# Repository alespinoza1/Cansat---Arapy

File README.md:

# Cansat - Arapy
Este repositorio contiene los archivos de diseño de placas electrónicas, modelos 3D, firmware y código fuente de la aplicación.

[proyecto arapy](http://www.proyectoarapy.com.py/)

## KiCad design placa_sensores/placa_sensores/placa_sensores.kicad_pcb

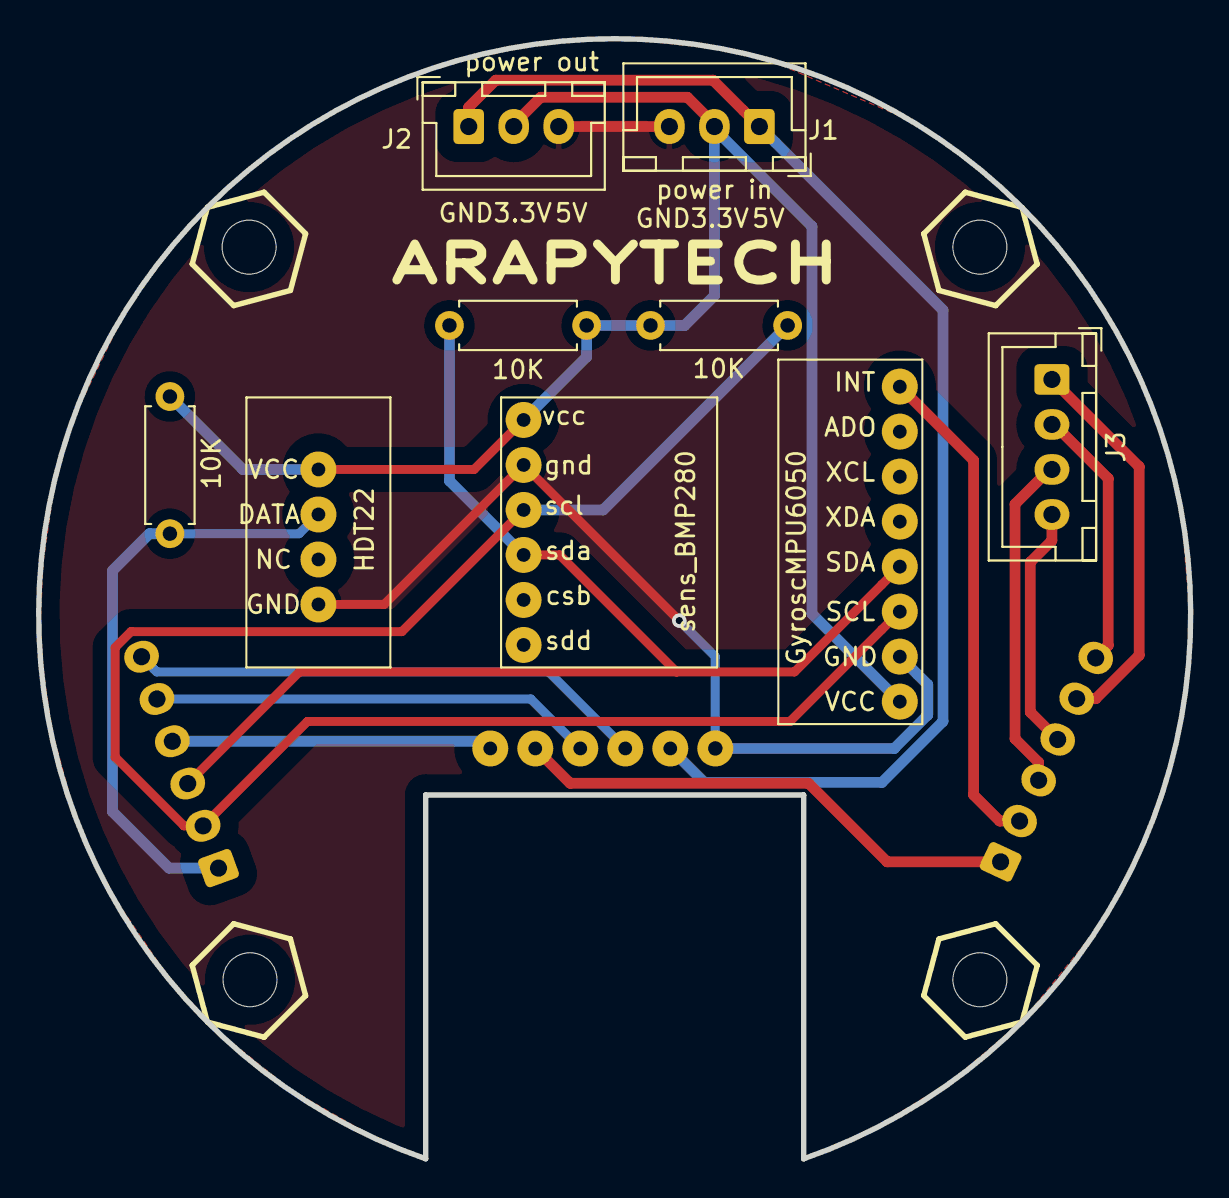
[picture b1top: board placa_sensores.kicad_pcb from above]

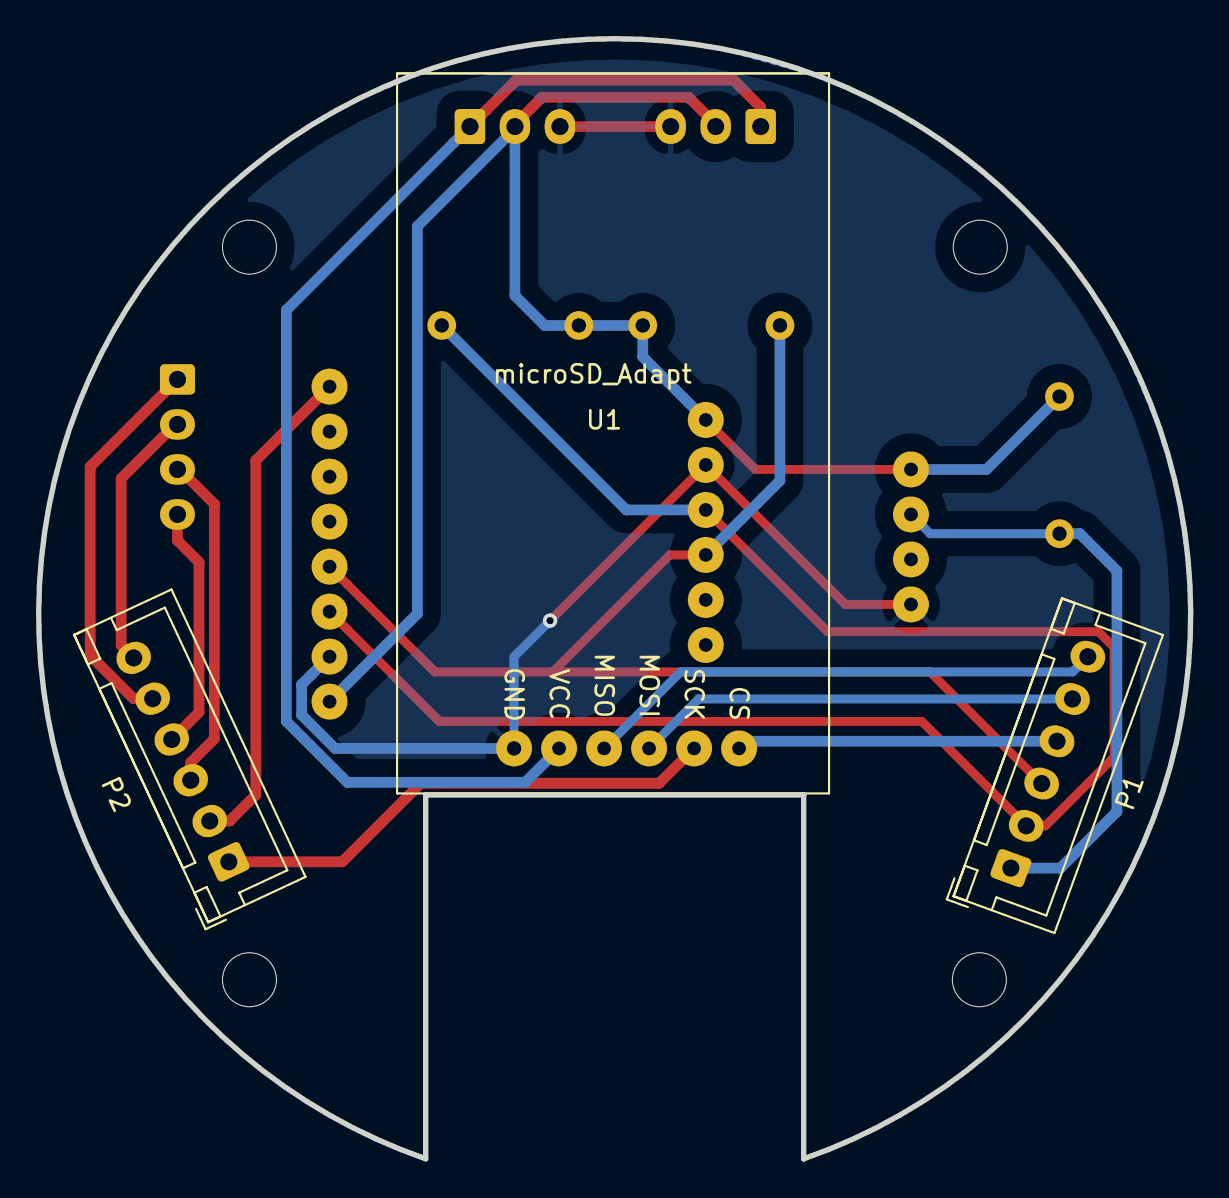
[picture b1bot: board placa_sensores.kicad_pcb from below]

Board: 2 copper layers, 64.0 x 62.2 mm, 10 parts (3 on the bottom side), 14 nets.

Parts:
10K, 10K#2: 10K; R_Axial_DIN0207_L6.3mm_D2.5mm_P7.62mm_Horizontal
10K#3: R; R_Axial_DIN0207_L6.3mm_D2.5mm_P7.62mm_Horizontal
HDT22: Sens_DHT22; DHT22
J1: power in; JST_XH_B3B-XH-A_1x03_P2.50mm_Vertical
J2: power out; JST_XH_B3B-XH-A_1x03_P2.50mm_Vertical
J3: Conn_01x04; JST_XH_B4B-XH-A_1x04_P2.50mm_Vertical
P1: Conector Señales 1; JST_XH_B6B-XH-A_1x06_P2.50mm_Vertical
P2: Conector Señales 2; JST_XH_B6B-XH-A_1x06_P2.50mm_Vertical
U1: microSD_Adapt; microSD

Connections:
3.3V: 10K.1, 10K#2.1, 10K#3.1, HDT22.1, J1.2, J2.2
5V: J1.1, J2.1, U1.2
CS: P1.4, U1.6
DGND: HDT22.4, J1.3, J2.3, U1.1
Dig1: J3.3, P2.3
MISO: P1.6, U1.3
MOSI: P1.5, U1.4
PWM: J3.4, P2.4
RESC: J3.2, P2.6
SCK: P2.1, U1.5
SCL: 10K.2, P1.2
SDA: 10K#2.2, P1.3
TEMP_SENS: 10K#3.2, HDT22.2, P1.1
TRANS: J3.1, P2.5

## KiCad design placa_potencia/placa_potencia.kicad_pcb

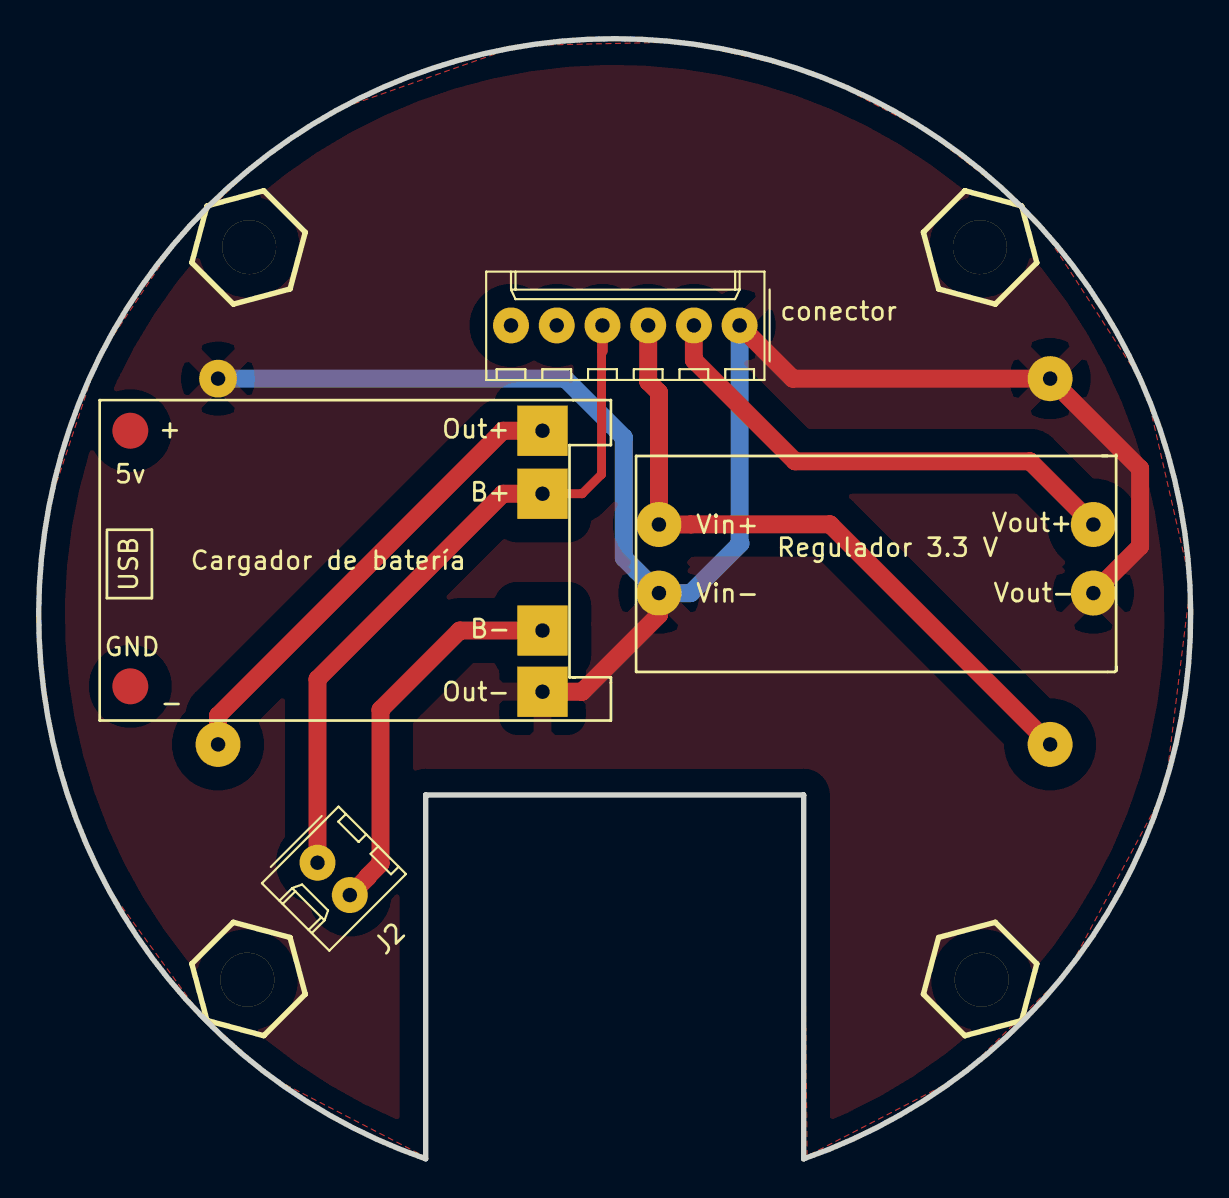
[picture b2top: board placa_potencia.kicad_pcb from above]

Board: 2 copper layers, 64.0 x 62.2 mm, 4 parts (1 on the bottom side), 4 nets.

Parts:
Elevador Boost : boost_5V; dc_dc_conv_xl60009
J2: Conn_01x02; Molex_KK-254_AE-6410-02A_1x02_P2.54mm_Vertical
Regulador 3.3 V : reg3_3V; AMS117_3_3V_MOD
conector: Conn_01x06_Male; Molex_KK-254_AE-6410-06A_1x06_P2.54mm_Vertical

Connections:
+BATT: J2.1, conector.4
/3.3V: Regulador 3.3 V.3, conector.2
/7V: Elevador Boost.3, Regulador 3.3 V.1, conector.3
Earth: Elevador Boost.2, Elevador Boost.4, Regulador 3.3 V.2, Regulador 3.3 V.4, conector.1

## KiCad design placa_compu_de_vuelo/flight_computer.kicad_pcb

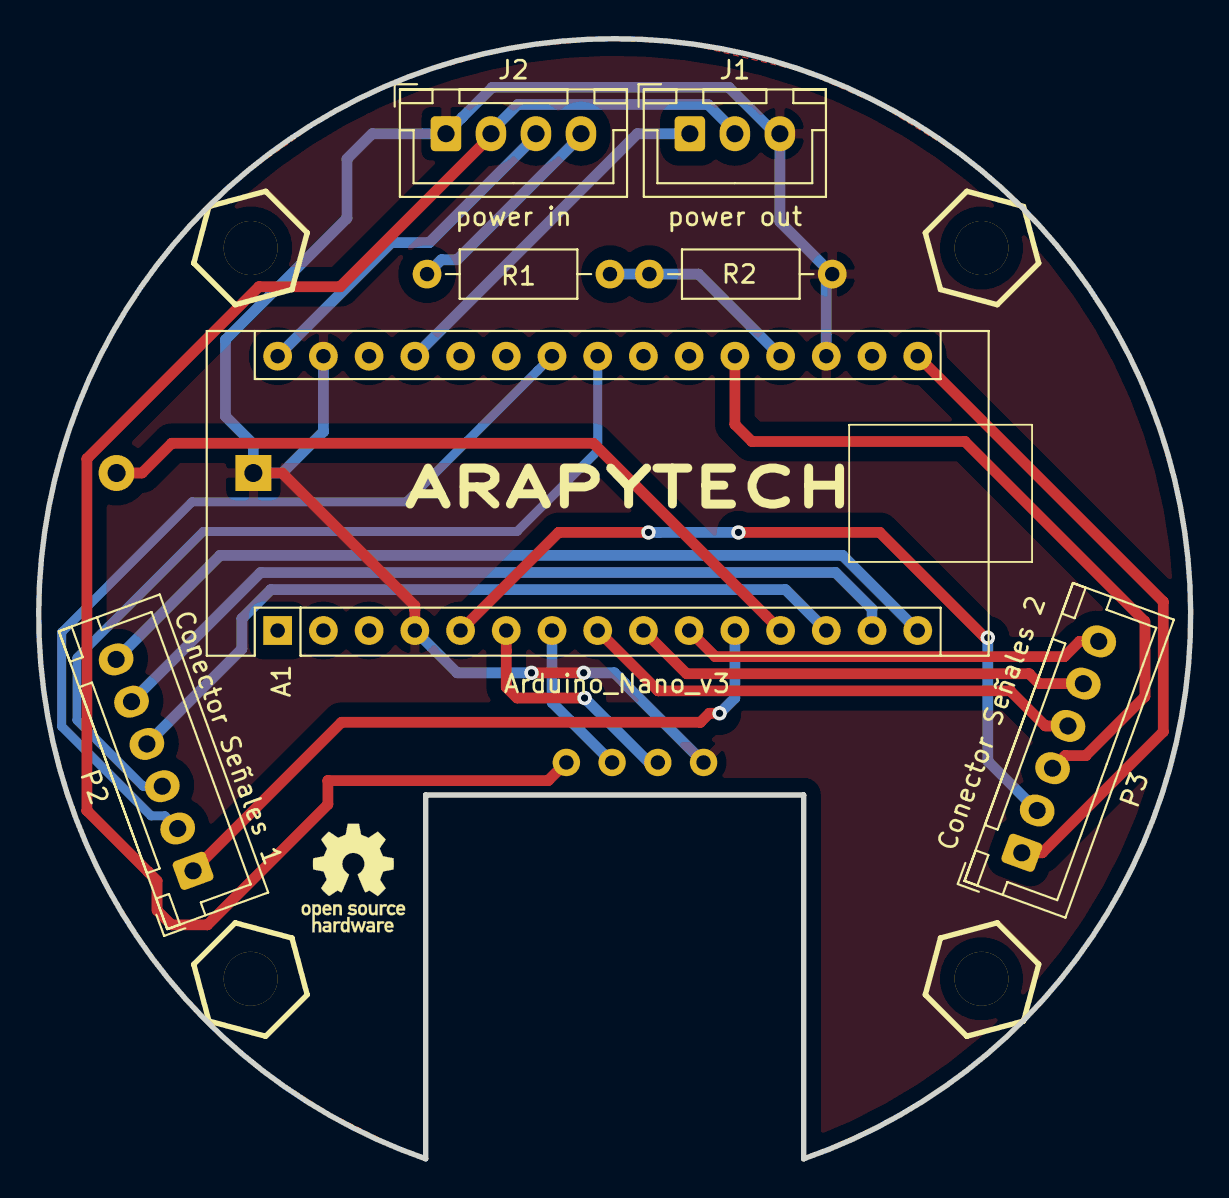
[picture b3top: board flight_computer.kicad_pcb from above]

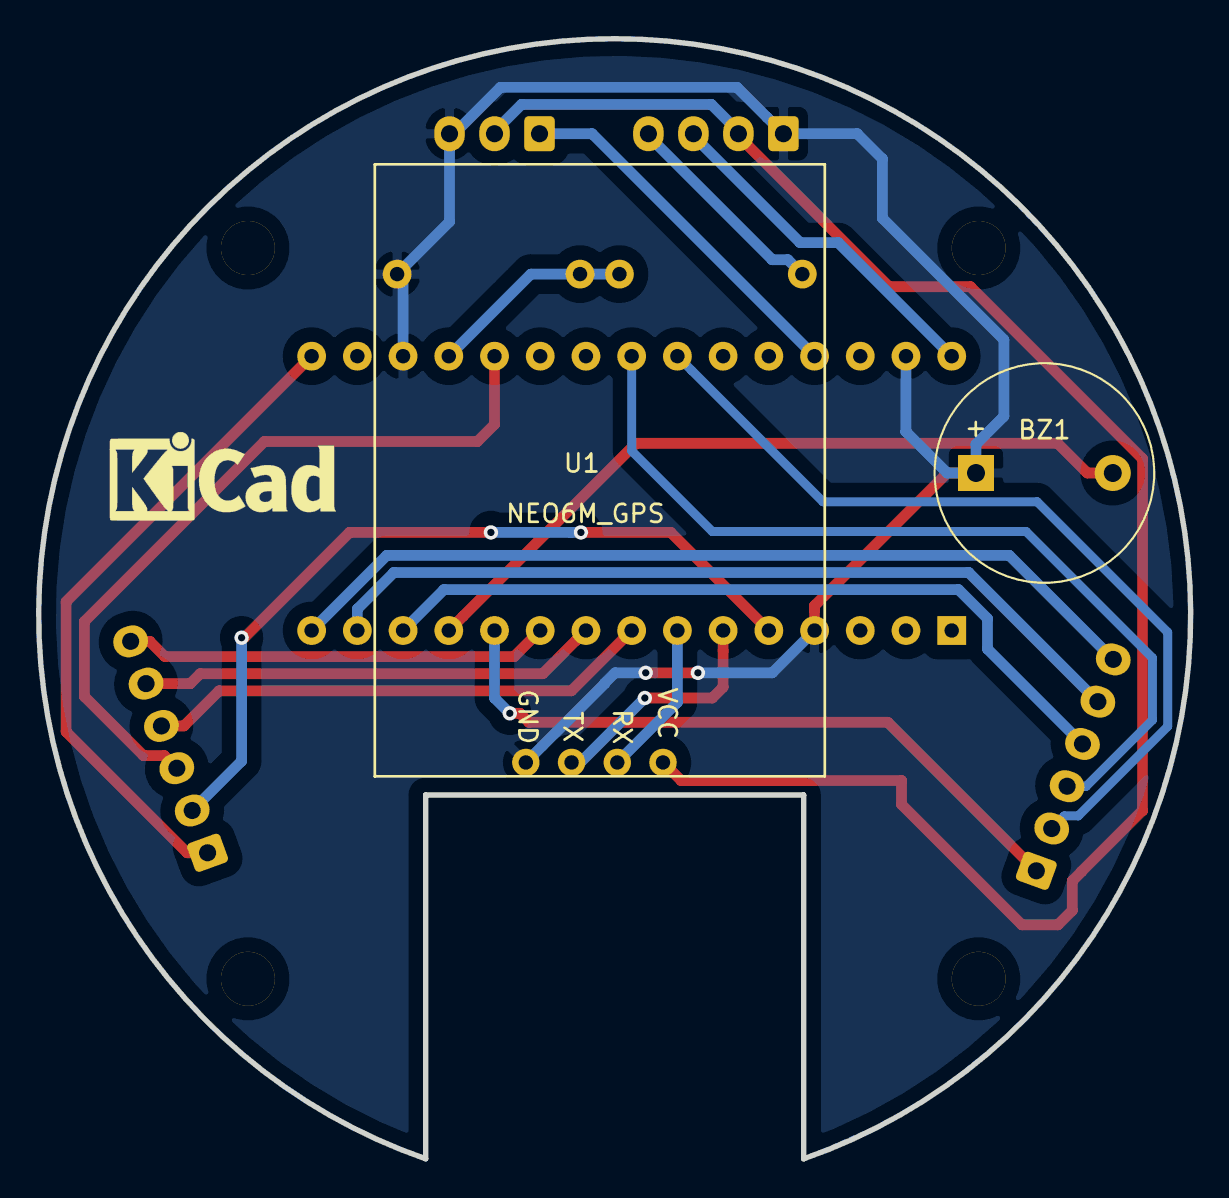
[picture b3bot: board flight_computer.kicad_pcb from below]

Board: 2 copper layers, 64.0 x 62.2 mm, 9 parts (2 on the bottom side), 21 nets.

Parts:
A1: Arduino_Nano_v3; Arduino_Nano
BZ1: Buzzer; Buzzer_12x9.5RM7.6
J1: power out; JST_XH_B3B-XH-A_1x03_P2.50mm_Vertical
J2: power in; JST_XH_B4B-XH-A_1x04_P2.50mm_Vertical
P2: Conector Señales 1; JST_XH_B6B-XH-A_1x06_P2.50mm_Vertical
P3: Conector Señales 2; JST_XH_B6B-XH-A_1x06_P2.50mm_Vertical
R1, R2: R; R_Axial_DIN0207_L6.3mm_D2.5mm_P10.16mm_Horizontal
U1: NEO6M_GPS; neo6m_gps

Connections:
3.3V: J1.2, J2.2, U1.4
5V: A1.27, J1.1
BATT: J2.4, R1.1
CS: A1.13, P2.4
DGND: A1.4, A1.18, A1.29, BZ1.1, J1.3, J2.1, R2.2, U1.1
Dig1: A1.20, P3.3
INT_GIROSC: A1.5, P3.2
MISO: A1.15, P2.6
MOSI: A1.14, P2.5
unnamed: A1.12, BZ1.2
unnamed: A1.19, R1.2, R2.1
PWM: A1.8, P3.4
RESC: A1.10, P3.6
RX_GPS: A1.6, U1.2
SCK: A1.16, P3.1
SCL: A1.24, P2.2
SDA: A1.23, P2.3
TEMP_SENS: A1.11, P2.1
TRANS: A1.9, P3.5
TX_GPS: A1.7, U1.3
VCC: A1.30, J2.3

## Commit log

2020-01-09 ensamblaje 3D
2020-01-10 placas electrónicas
2020-07-13 se agregaron los archivos de pcbs
